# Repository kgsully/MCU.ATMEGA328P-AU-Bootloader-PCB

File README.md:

# ATMEGA328P-AU Bootloader Burn PCB
 PCB to Burn Bootlader to Bare ATMEGA328P-AU Chips
 
 Please refer to the README docx or PDF found in the documentation folder for further information.

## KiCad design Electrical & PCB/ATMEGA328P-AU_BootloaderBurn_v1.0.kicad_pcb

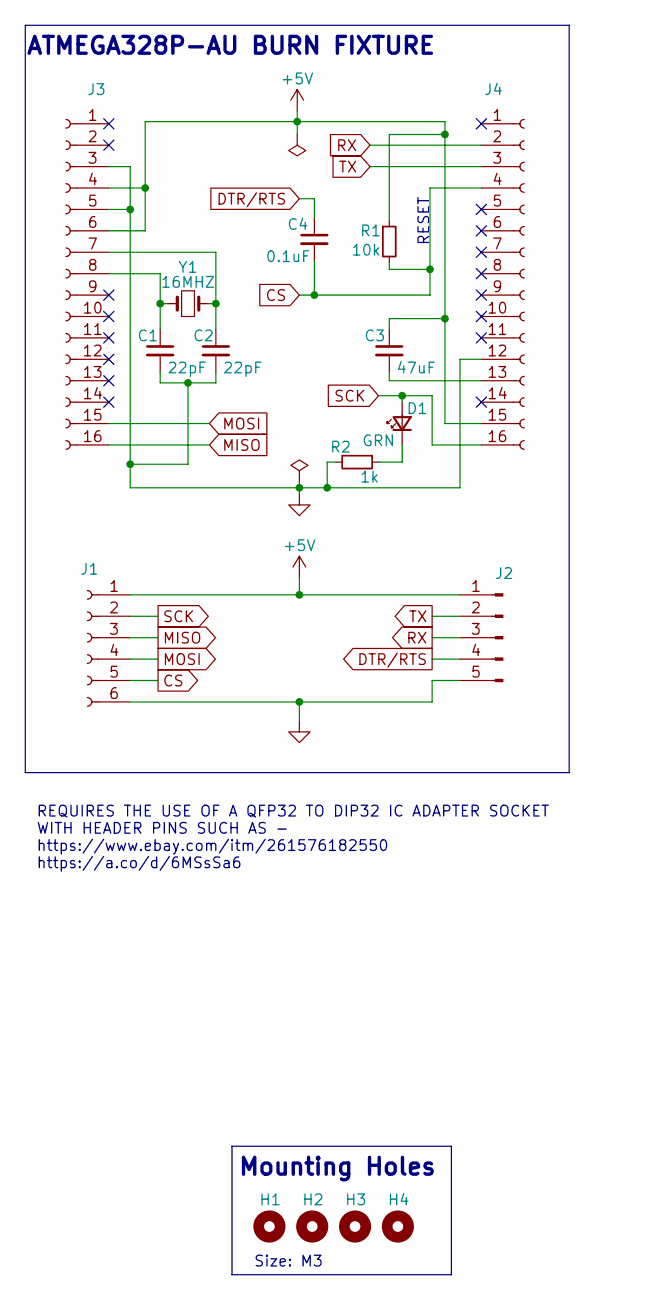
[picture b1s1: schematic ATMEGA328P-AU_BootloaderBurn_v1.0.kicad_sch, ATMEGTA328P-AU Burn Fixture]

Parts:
C1, C2: 22pF; C_0603_1608Metric
C3: 47uF; C_0805_2012Metric
C4: 0.1uF; C_0603_1608Metric
D1: GRN; LED_D5.0mm
H1, H2, H3, H4: MountingHole; MountingHole_3.2mm_M3
J1: Conn_01x06_Female; PinSocket_1x06_P2.54mm_Vertical
J2: Conn_01x05_Male; PinHeader_1x05_P2.54mm_Vertical
J3, J4: Conn_01x16_Female; PinSocket_1x16_P2.54mm_Vertical
R1: 10k; R_0603_1608Metric
R2: 1k; R_0603_1608Metric
Y1: 16MHZ; Crystal_HC49-U_Vertical

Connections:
+5V: C3.1, J1.1, J2.1, J3.4, J3.6, J4.15, R1.1
CS: C4.2, J1.5, J4.4, R1.2
DTR/RTS: C4.1, J2.4
GND: C1.2, C2.2, J1.6, J2.5, J3.3, J3.5, J4.12, R2.2
MISO: J1.3, J3.16
MOSI: J1.4, J3.15
unnamed: C1.1, J3.8, Y1.2
unnamed: C2.1, J3.7, Y1.1
unnamed: C3.2, J4.13
unnamed: D1.1 (K), R2.1
RX: J2.3, J4.2
SCK: D1.2 (A), J1.2, J4.16
TX: J2.2, J4.3

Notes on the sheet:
RESET
REQUIRES THE USE OF A QFP32 TO DIP32 IC ADAPTER SOCKET WITH HEADER PINS SUCH AS - https://www.ebay.com/itm/261576182550 https://a.co/d/6MSsSa6
ATMEGA328P-AU BURN FIXTURE
Mounting Holes
Size: M3

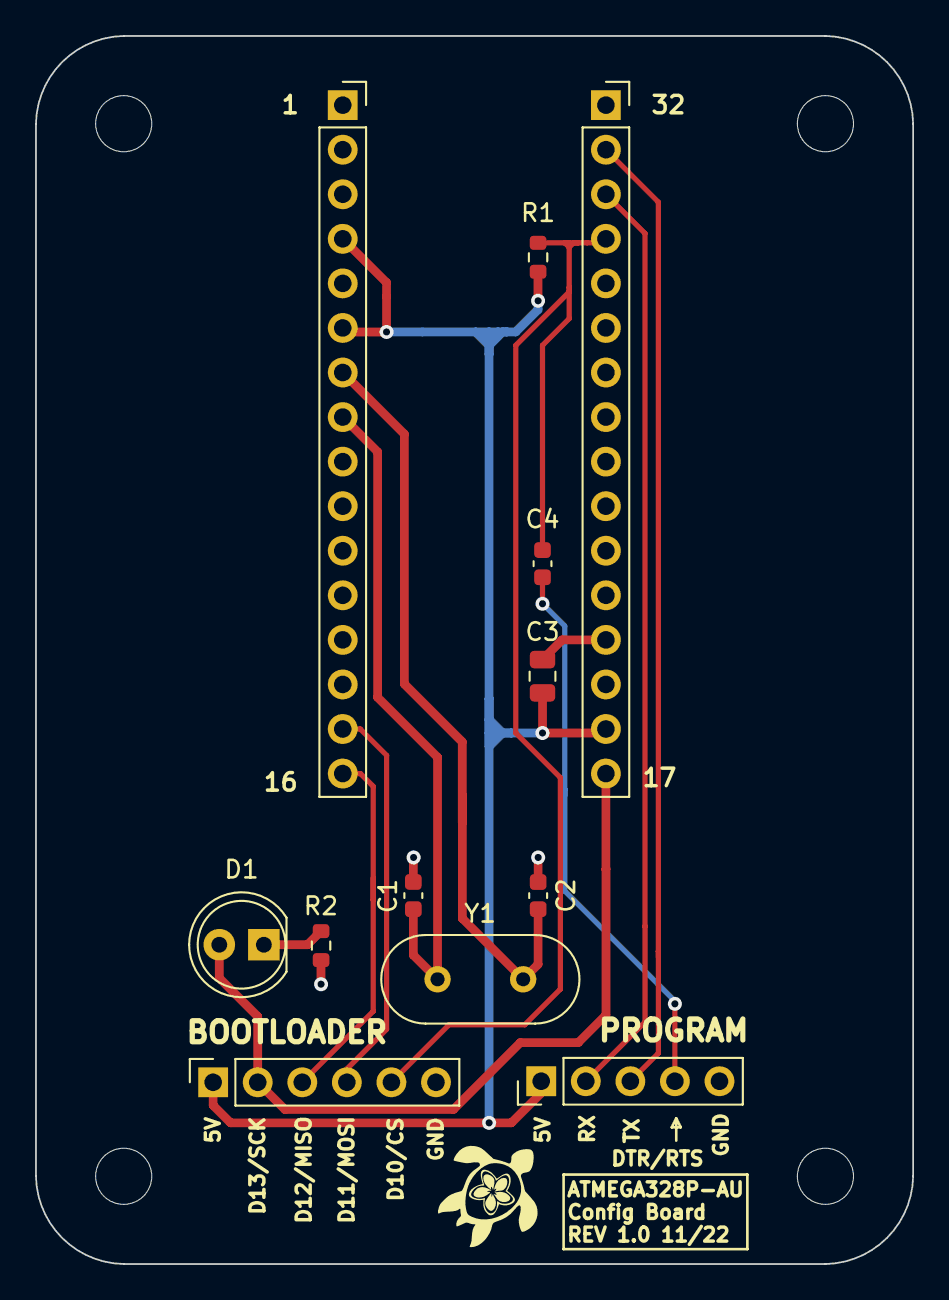
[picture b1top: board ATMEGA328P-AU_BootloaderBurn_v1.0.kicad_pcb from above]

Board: 2 copper layers, 50.0 x 70.0 mm, 16 parts (0 on the bottom side), 13 nets.
